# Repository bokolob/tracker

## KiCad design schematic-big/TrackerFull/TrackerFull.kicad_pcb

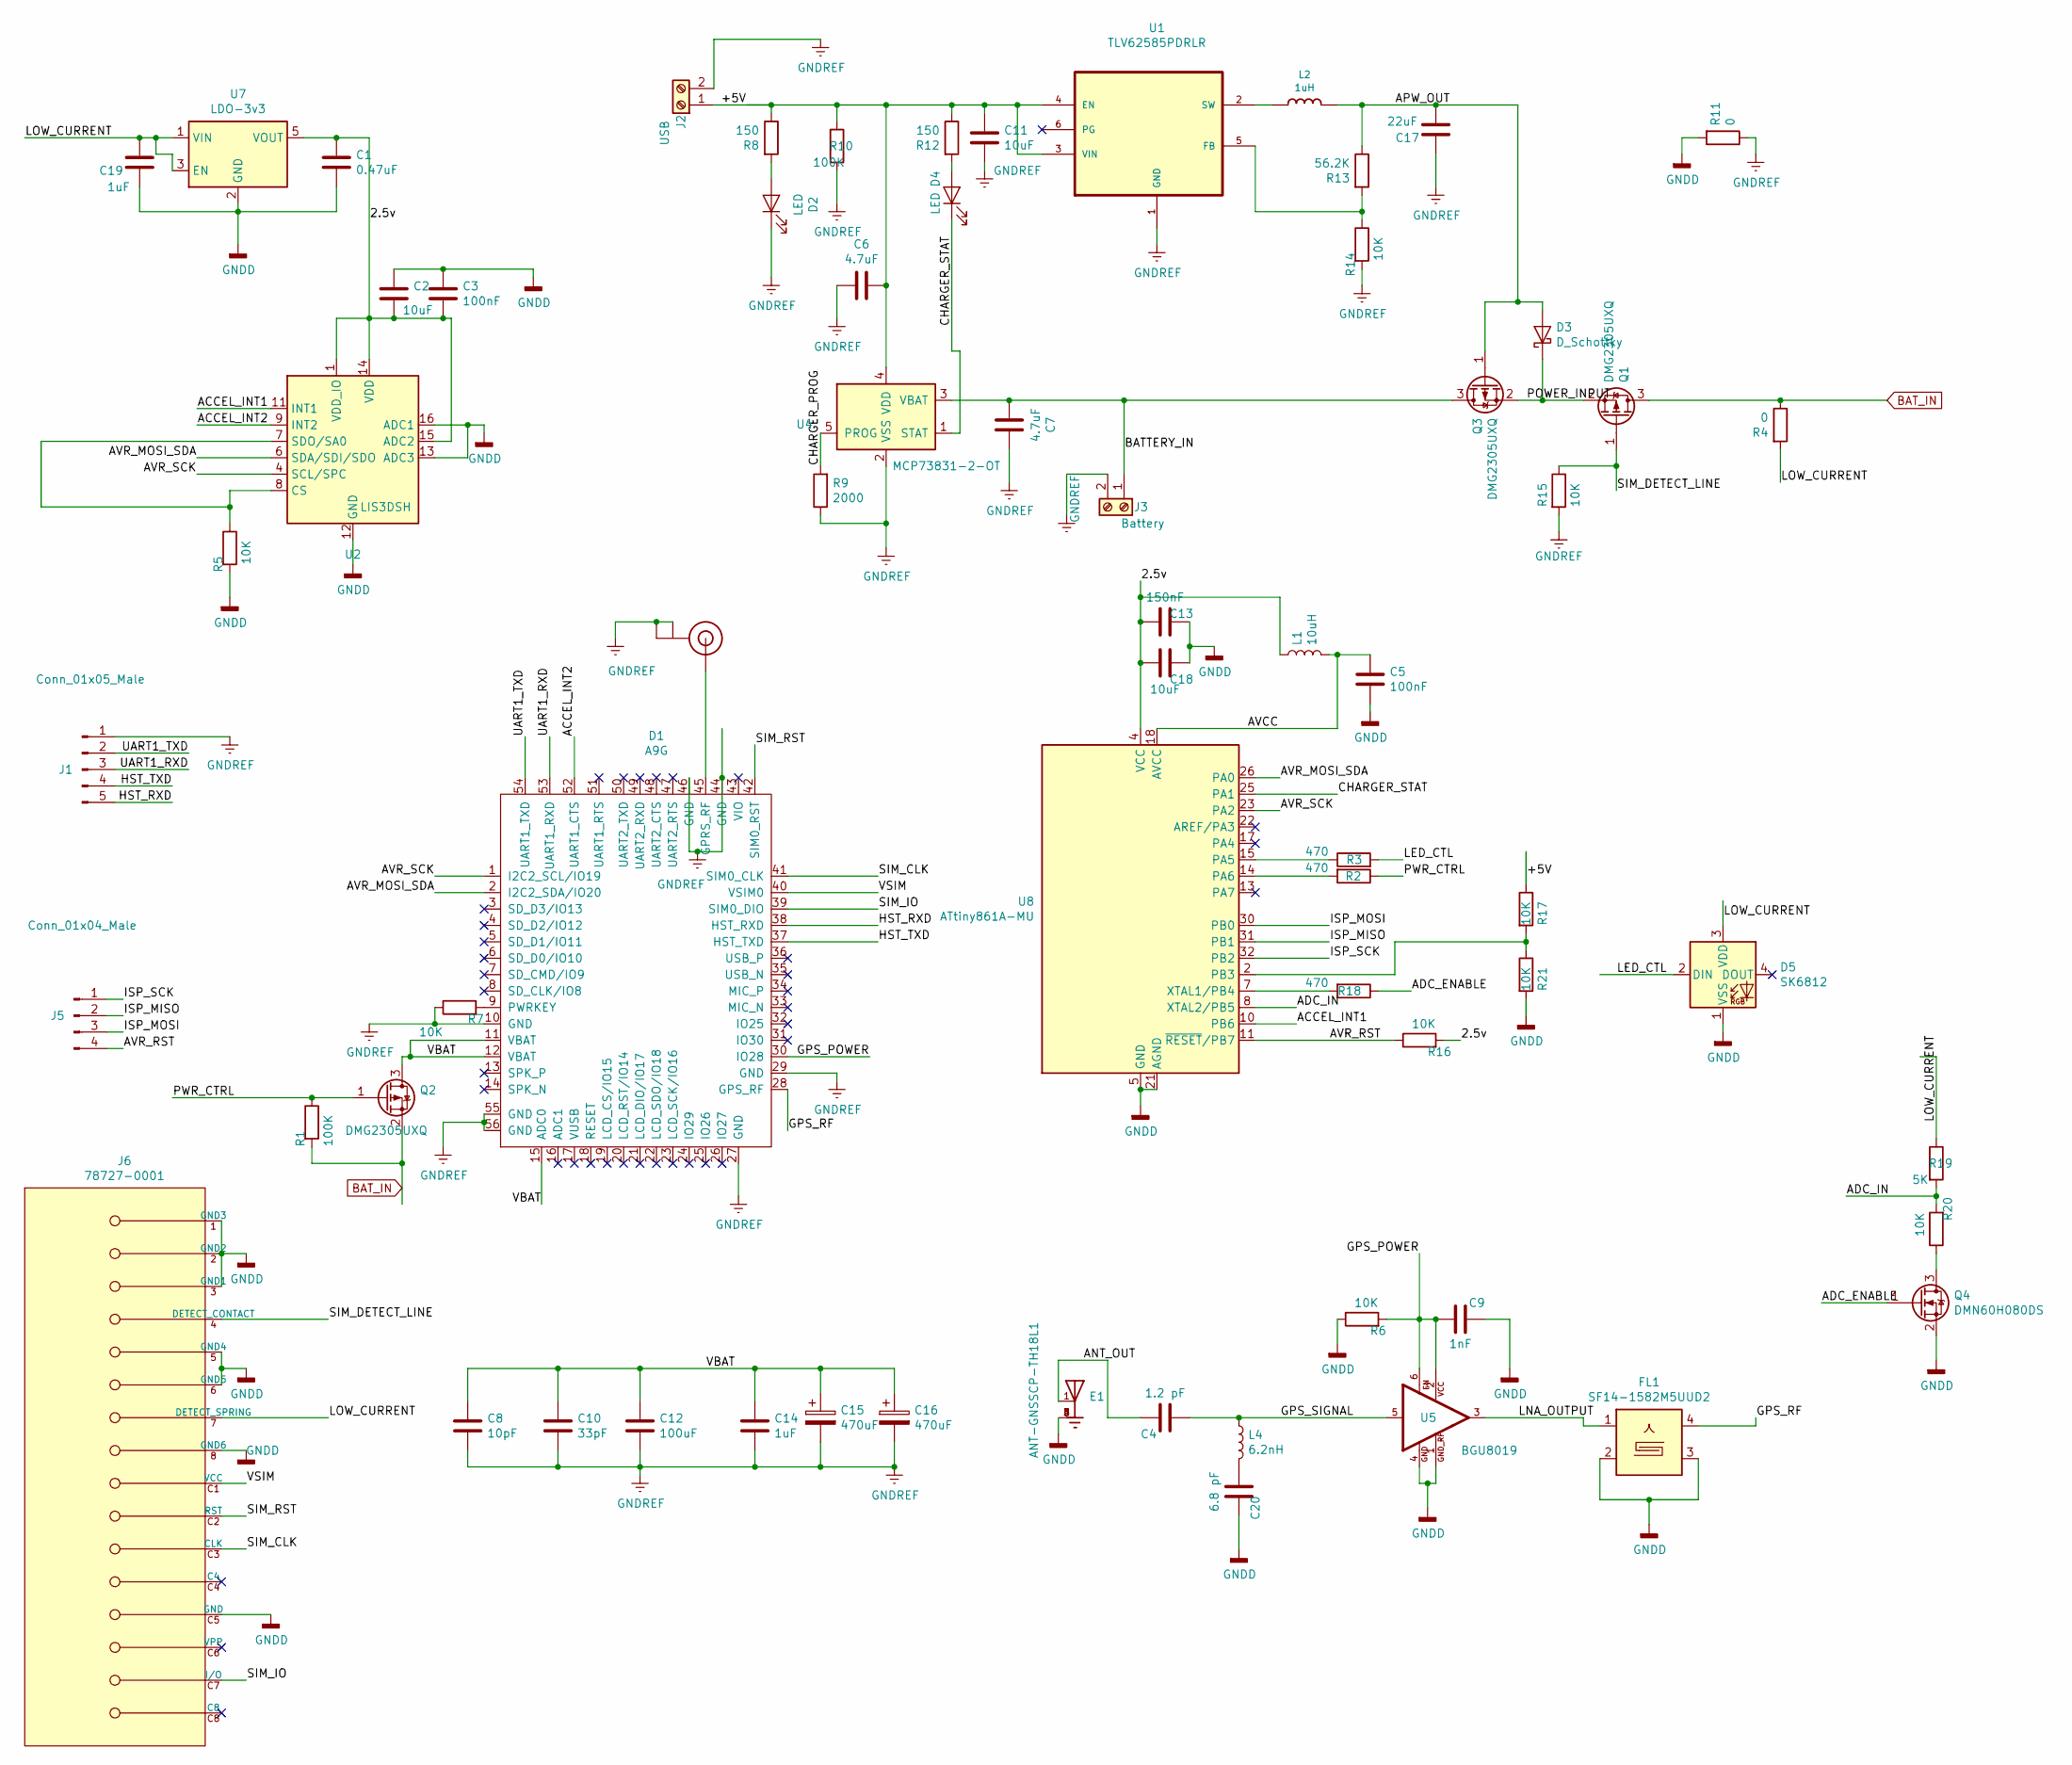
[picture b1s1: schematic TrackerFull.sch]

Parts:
C1: 0.47uF; C_0603_1608Metric
C2, C11, C18: 10uF; C_0603_1608Metric
C3, C5: 100nF; C_0402_1005Metric
C4: 1.2 pF; C_0402_1005Metric
C6, C7: 4.7uF; C_0603_1608Metric
C8: 10pF; C_0402_1005Metric
C9: 1nF; C_0402_1005Metric
C10: 33pF; C_0402_1005Metric
C12: 100uF; CP_EIA-6032-28_Kemet-C
C13: 150nF; C_0402_1005Metric
C14, C19: 1uF; C_0603_1608Metric
C15, C16: 470uF; CP_Elec_8x10.5
C17: 22uF; C_0805_2012Metric
C20: 6.8 pF; C_0402_1005Metric
D1: A9G; A9
D2, D4: LED; LED_0603_1608Metric_Pad1.05x0.95mm_HandSolder
D3: D_Schottky; D_SMA
D5: SK6812; LED_SK6812_PLCC4_5.0x5.0mm_P3.2mm
E1: ANT-GNSSCP-TH18L1; XDCR_ANT-GNSSCP-TH18L1
FL1: SF14-1582M5UUD2; Filter_1411-5_1.4x1.1mm
J1: Conn_01x05_Male; PinHeader_1x05_P2.54mm_Vertical
J2: USB; SolderWirePad_1x02_P3.81mm_Drill0.8mm
J3: Battery; SolderWirePad_1x02_P3.81mm_Drill0.8mm
J5: Conn_01x04_Male; PinHeader_1x04_P2.54mm_Vertical
J6: 78727-0001; Molex-78727-0001-0-0-MFG
L1: 10uH; L_0603_1608Metric
L2: 1uH; L_Vishay_IHLP-2020
L4: 6.2nH; L_0402_1005Metric
Q1, Q2, Q3: DMG2305UXQ; SOT-23
Q4: DMN60H080DS; SOT-23
R1, R10: 100K; R_0603_1608Metric
R2, R3, R18: 470; R_0402_1005Metric
R4, R11: 0; R_0402_1005Metric
R5, R6, R7, R14, R15, R16, R17, R20: 10K; R_0603_1608Metric
R8, R12: 150; R_0402_1005Metric
R9: 2000; R_0402_1005Metric
R13: 56.2K; R_0603_1608Metric
R19: 5K; R_0402_1005Metric
R21: 10K; R_0402_1005Metric
U1: TLV62585PDRLR; SOT50P160X60-6N
U2: LIS3DSH; LGA-16_3x3mm_P0.5mm_LayoutBorder3x5y
U4: MCP73831-2-OT; SOT-23-5
U5: BGU8019; SOT1232
U6: U.FL
U7: LDO-3v3; SOT-23-5
U8: ATtiny861A-MU; QFN-32-1EP_5x5mm_P0.5mm_EP3.1x3.1mm

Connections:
/2.5v: C1.1, C2.2, C3.2, C13.2, C18.2, L1.1, R16.2, U2.1 (VDD_IO), U2.14 (VDD), U2.15 (ADC2), U7.5 (VOUT), U8.4 (VCC)
/+5V: C6.2, C11.1, J2.1, R8.1, R10.1, R12.1, R17.1, U1.3 (VIN), U1.4 (EN), U4.4 (VDD)
/ACCEL_INT1: U2.11 (INT1), U8.10 (PB6)
/ACCEL_INT2: D1.52 (UART1_CTS), U2.9 (INT2)
/ADC_ENABLE: Q4.1 (G), R18.1
/ADC_IN: R19.2, R20.2, U8.8 (XTAL2/PB5)
/ANT_OUT: C4.2, E1.1
/APW_OUT: C17.1, D3.2 (A), L2.2, Q3.1 (G), R13.1
/AVCC: C5.1, L1.2, U8.18 (AVCC)
/AVR_MOSI_SDA: D1.2 (I2C2_SDA/IO20), U2.6 (SDA/SDI/SDO), U8.26 (PA0)
/AVR_RST: J5.4, R16.1, U8.11 (~RESET~/PB7)
/AVR_SCK: D1.1 (I2C2_SCL/IO19), U2.4 (SCL/SPC), U8.23 (PA2)
/BATTERY_IN: C7.1, J3.1, Q3.3 (D), U4.3 (VBAT)
/CHARGER_PROG: R9.2, U4.5 (PROG)
/CHARGER_STAT: D4.1 (K), U4.1 (STAT), U8.25 (PA1)
/GPS_POWER: C9.1, D1.30 (IO28), R6.2, U5.2, U5.6
/GPS_RF: D1.28 (GPS_RF), FL1.4
/GPS_SIGNAL: C4.1, L4.1, U5.5
/HST_RXD: D1.38 (HST_RXD), J1.5
/HST_TXD: D1.37 (HST_TXD), J1.4
/ISP_MISO: J5.2, U8.31 (PB1)
/ISP_MOSI: J5.3, U8.30 (PB0)
/ISP_SCK: J5.1, U8.32 (PB2)
/LED_CTL: D5.2 (DIN), R3.2
/LNA_OUTPUT: FL1.1, U5.3
/LOW_CURRENT: C19.1, D5.3 (VDD), J6.7 (DETECT_SPRING), R4.2, R19.1, U7.1 (VIN), U7.3 (EN)
/POWER_INPUT: D3.1 (K), Q1.2 (S), Q3.2 (S)
/PWR_CTRL: Q2.1 (G), R1.1, R2.1
/SIM_CLK: D1.41 (SIM0_CLK), J6.C3 (CLK)
/SIM_DETECT_LINE: J6.4 (DETECT_CONTACT), Q1.1 (G), R15.1
/SIM_IO: D1.39 (SIM0_DIO), J6.C7 (I/O)
/SIM_RST: D1.42 (SIM0_RST), J6.C2 (RST)
/UART1_RXD: D1.53 (UART1_RXD), J1.3
/UART1_TXD: D1.54 (UART1_TXD), J1.2
/VBAT: C8.1, C10.1, C12.1, C14.1, C15.1, C16.1, D1.11 (VBAT), D1.12 (VBAT), D1.15 (ADC0), Q2.3 (D)
/VSIM: D1.40 (VSIM0), J6.C1 (VCC)
BAT_IN: Q1.3 (D), Q2.2 (S), R1.2, R4.1
GNDD: C1.2, C2.1, C3.1, C5.2, C9.2, C13.1, C18.1, C19.2, C20.2, D5.1 (VSS), E1.2, E1.3, E1.4, E1.5, FL1.2, FL1.3, FL1.5, J6.1 (GND3), J6.2 (GND2), J6.3 (GND1), J6.5 (GND4), J6.6 (GND5), J6.8 (GND6), J6.C5 (GND), Q4.2 (S), R5.2, R6.1, R11.2, R21.2, U2.5 (GND), U2.10 (GND), U2.12 (GND), U2.13 (ADC3), U2.16 (ADC1), U5.1, U5.4, U7.2 (GND), U8.5 (GND), U8.21 (AGND), U8.33 (GND)
GNDREF: C6.1, C7.2, C8.2, C10.2, C11.2, C12.2, C14.2, C15.2, C16.2, C17.2, D1.10 (GND), D1.27 (GND), D1.29 (GND), D1.44 (GND), D1.46 (GND), D1.55 (GND), D1.56 (GND), D2.1 (K), J1.1, J2.2, J3.2, R7.1, R9.1, R10.2, R11.1, R14.2, R15.2, U1.1 (GND), U4.2 (VSS), U6.1 (GND@0), U6.2 (GND@1)
unnamed: C20.1, L4.2
unnamed: D1.9 (PWRKEY), R7.2
unnamed: D1.45 (GPRS_RF), U6.3 (SIGNAL)
unnamed: D2.2 (A), R8.2
unnamed: D4.2 (A), R12.2
unnamed: L2.1, U1.2 (SW)
unnamed: Q4.3 (D), R20.1
unnamed: R2.2, U8.14 (PA6)
unnamed: R3.1, U8.15 (PA5)
unnamed: R5.1, U2.7 (SDO/SA0), U2.8 (CS)
unnamed: R13.2, R14.1, U1.5 (FB)
unnamed: R17.2, R21.1, U8.2 (PB3)
unnamed: R18.2, U8.7 (XTAL1/PB4)

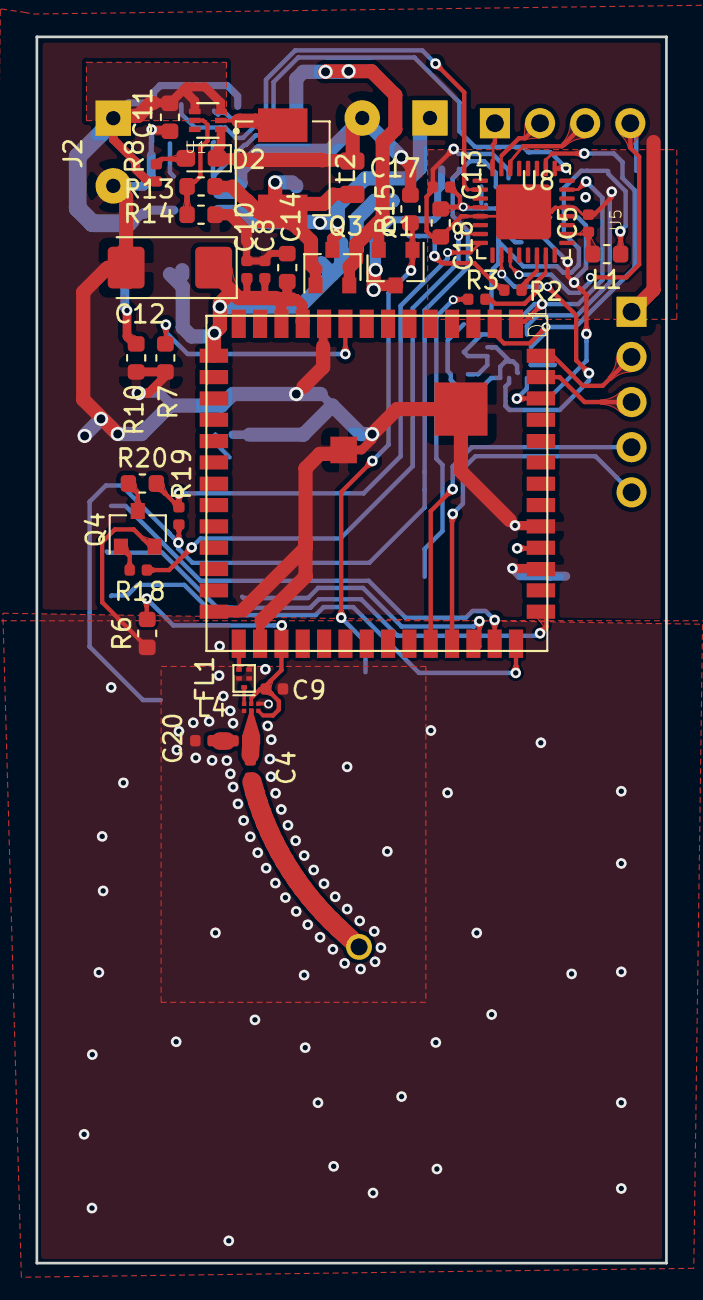
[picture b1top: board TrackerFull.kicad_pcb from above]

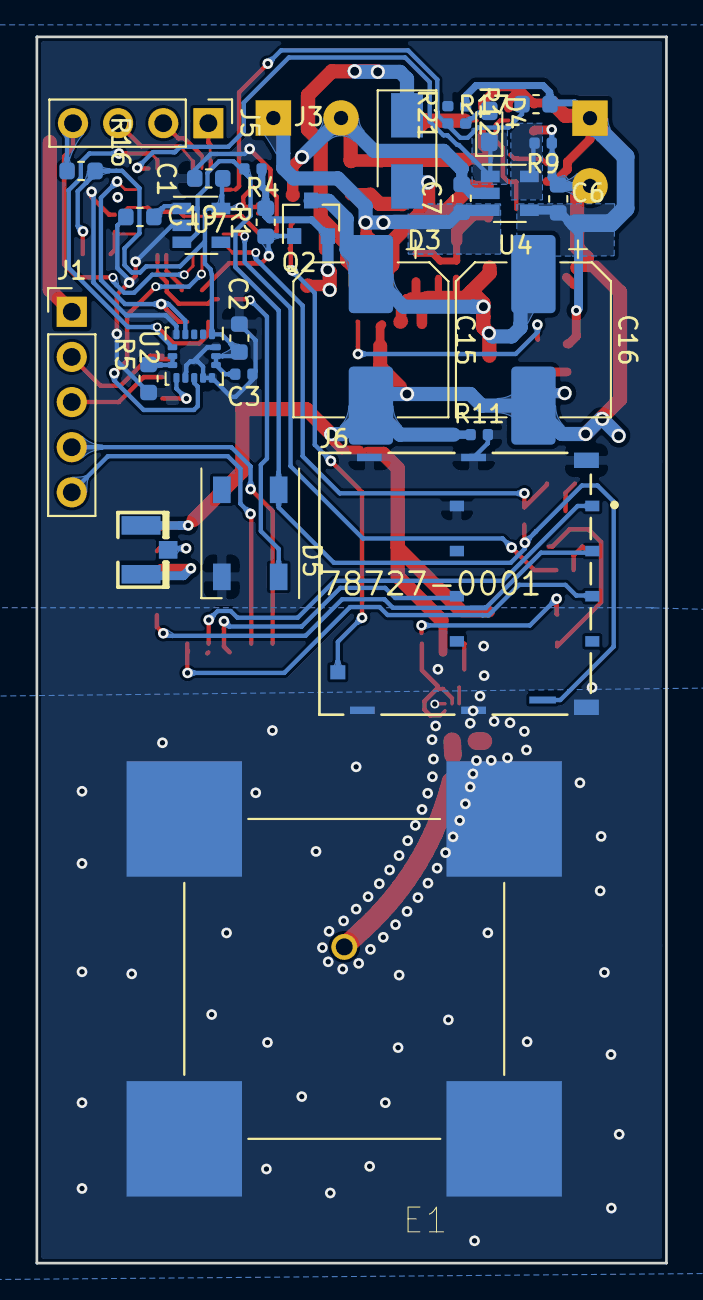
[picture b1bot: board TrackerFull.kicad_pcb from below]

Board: 2 copper layers, 35.4 x 69.0 mm, 67 parts (30 on the bottom side), 52 nets.

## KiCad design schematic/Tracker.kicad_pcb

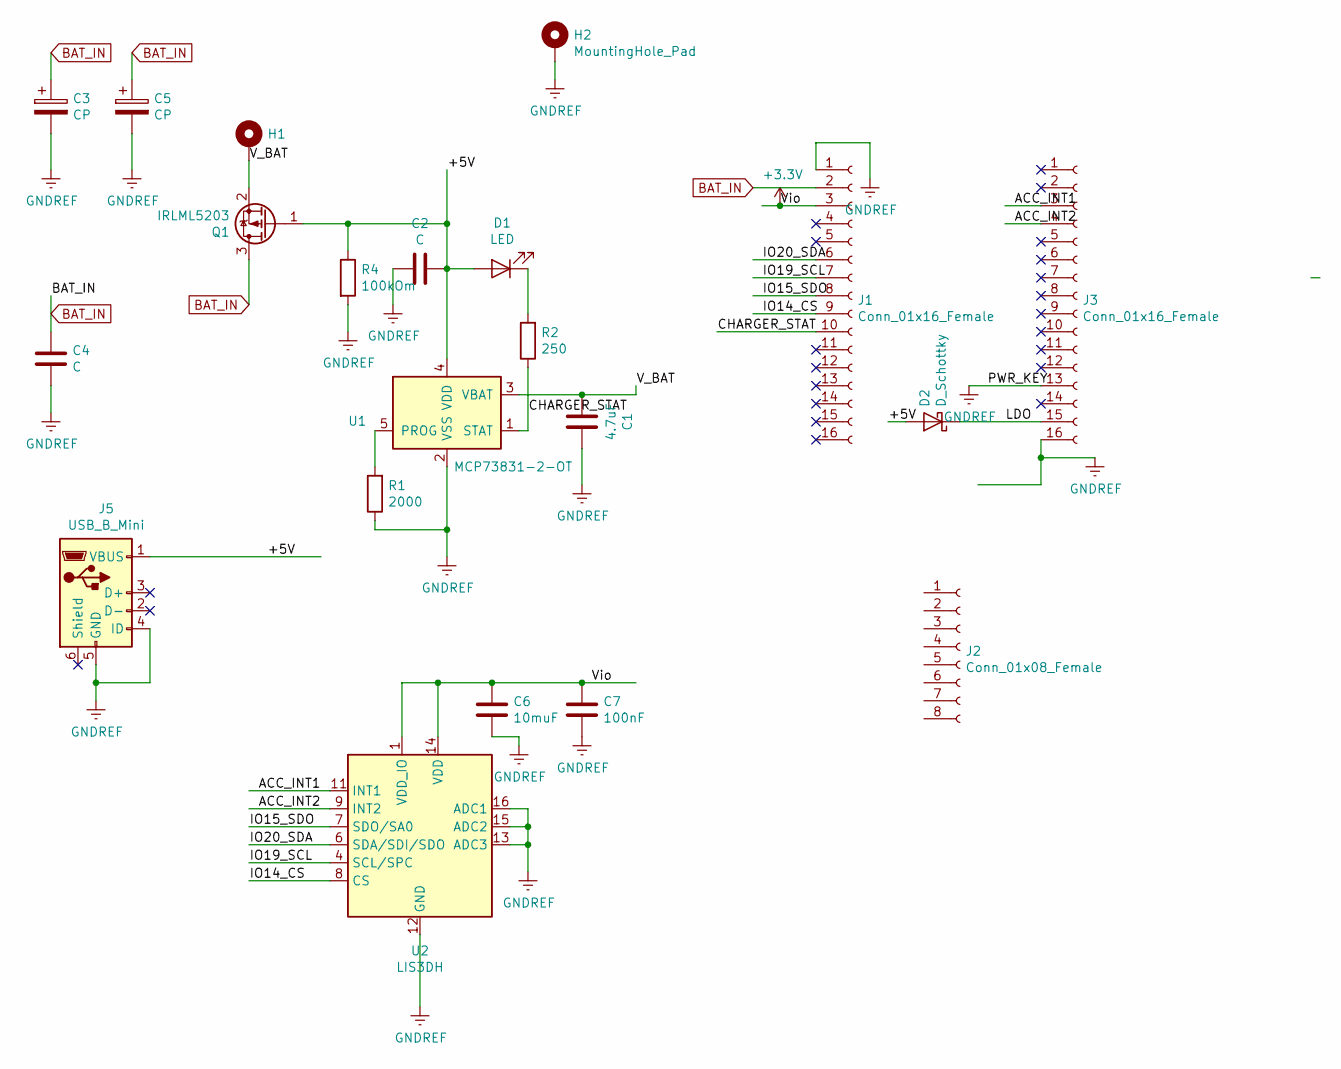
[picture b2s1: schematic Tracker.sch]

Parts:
C1: 4.7uF; CP_Radial_D4.0mm_P2.00mm
C2: C; CP_Radial_D4.0mm_P2.00mm
C3, C5: CP; CP_Radial_D8.0mm_P3.50mm
C4: C; CP_EIA-3216-18_Kemet-A
C6: 10muF; C_Disc_D3.4mm_W2.1mm_P2.50mm
C7: 100nF; C_Disc_D3.4mm_W2.1mm_P2.50mm
D1: LED; LED_D3.0mm
D2: D_Schottky; D_SMA
H1, H2: MountingHole_Pad; MountingHole_2.2mm_M2_DIN965_Pad
J1, J3: Conn_01x16_Female; PinSocket_1x16_P2.54mm_Vertical
J2: Conn_01x08_Female; PinHeader_1x08_P2.54mm_Vertical
J5: USB_B_Mini; USB_Micro-B_Molex-105017-0001
Q1: IRLML5203; SOT-23
R1: 2000; R_0603_1608Metric
R2: 250; R_0402_1005Metric
R4: 100kOm; R_0603_1608Metric
U1: MCP73831-2-OT; SOT-23-5
U2: LIS3DH; LGA-16_3x3mm_P0.5mm_LayoutBorder3x5y

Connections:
+3V3: C6.1, C7.1, J1.3, U2.1 (VDD_IO), U2.14 (VDD)
/+5V: C2.2, D1.2 (A), D2.2 (A), J5.1 (VBUS), Q1.1 (G), R4.1, U1.4 (VDD)
/ACC_INT1: J3.3, U2.11 (INT1)
/ACC_INT2: J3.4, U2.9 (INT2)
/CHARGER_STAT: J1.10, R2.1, U1.1 (STAT)
/IO14_CS: J1.9, U2.8 (CS)
/IO15_SDO: J1.8, U2.7 (SDO/SA0)
/IO19_SCL: J1.7, U2.4 (SCL/SPC)
/IO20_SDA: J1.6, U2.6 (SDA/SDI/SDO)
/LDO: D2.1 (K), J3.15
/V_BAT: C1.1, H1.1, Q1.2 (S), U1.3 (VBAT)
BAT_IN: C3.1, C4.1, C5.1, J1.2, Q1.3 (D)
GNDREF: C1.2, C2.1, C3.2, C4.2, C5.2, C6.2, C7.2, H2.1, J1.1, J3.13, J3.16, J5.4 (ID), J5.5 (GND), R1.1, R4.2, U1.2 (VSS), U2.5 (GND), U2.10 (GND), U2.12 (GND), U2.13 (ADC3), U2.15 (ADC2), U2.16 (ADC1)
unnamed: D1.1 (K), R2.2
unnamed: R1.2, U1.5 (PROG)

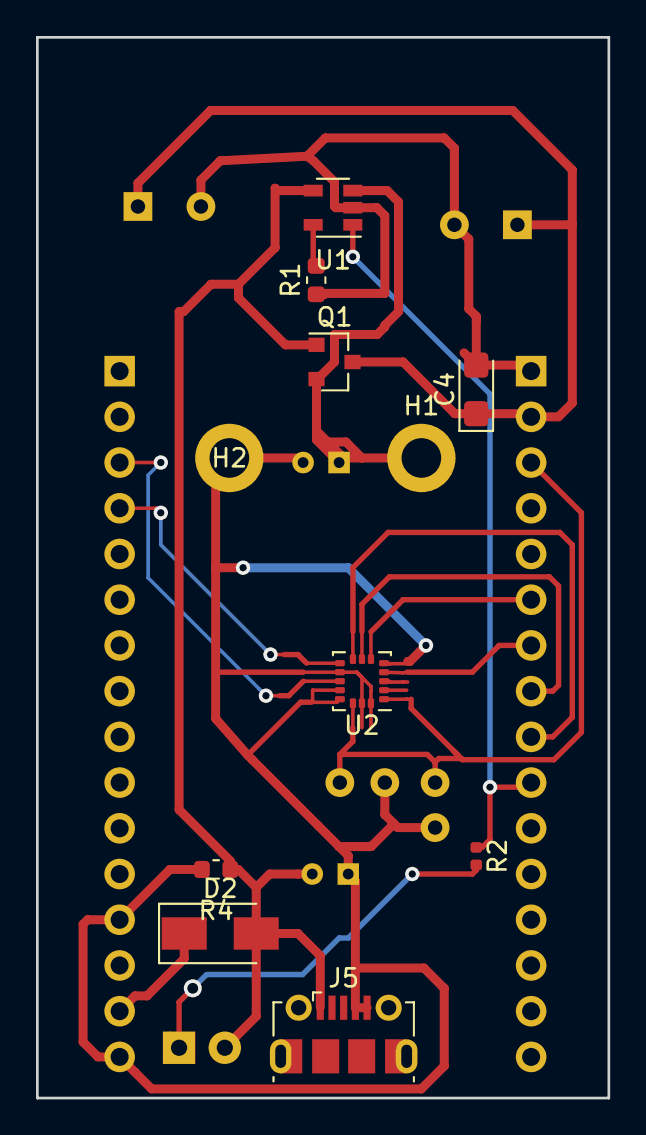
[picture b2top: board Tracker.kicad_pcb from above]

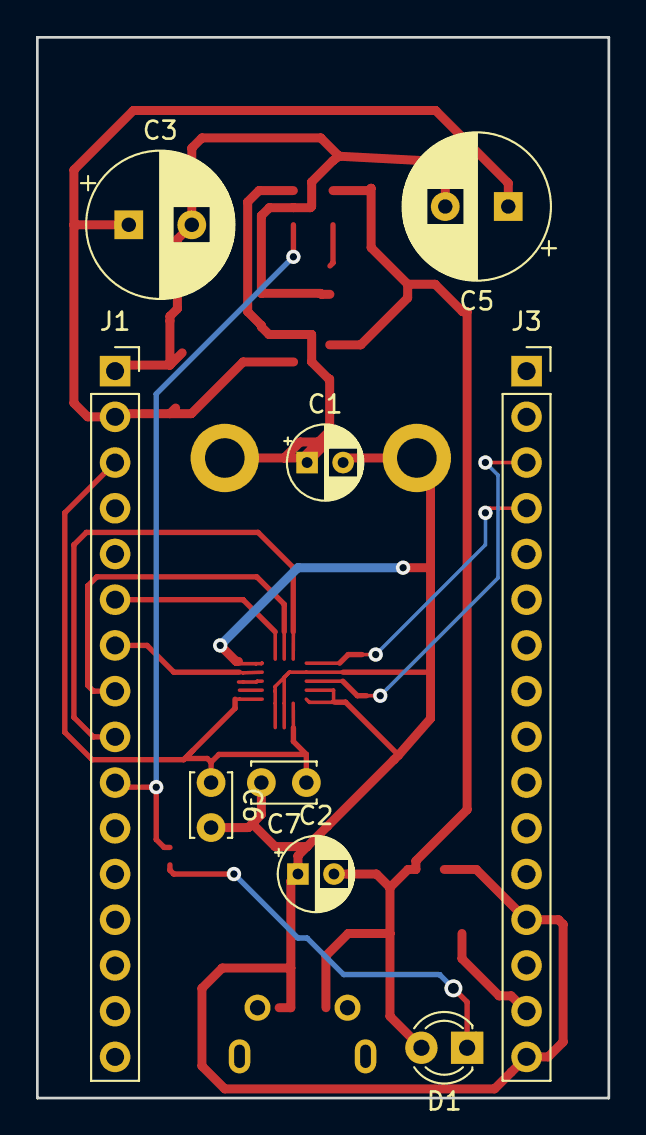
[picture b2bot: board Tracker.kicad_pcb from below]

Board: 2 copper layers, 31.8 x 58.9 mm, 20 parts (9 on the bottom side), 15 nets.

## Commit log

2020-07-17 Lis3dsh accel driver
2020-07-28 Schematics
2020-08-07 multiple improvements
2020-09-09 Sms commands and refactorings
2020-09-10 New schematic
2020-09-10 schematic.png
2020-09-10 schematic fixes
2020-09-14 bug fixes
2020-09-19 schematic update
2020-09-30 Software i2c
2020-10-08 Last avr firmvare
2020-10-08 Last schematic
2020-10-12 latest version. Doesnt work :)
2020-10-13 last changes
2020-10-17 new schematic picture
2020-10-22 schematic updated
2020-10-26 next milestone
2020-10-28 GPS antenna on pcb
2020-10-30 updated schematic
2020-11-06 Last schematic changes
2020-11-08 schematics update
2020-11-10 replaced attiny
2020-11-14 pcb layout
2020-11-20 attiny461 code update and new a9g footprint
2020-11-21 last schematic update
2020-12-05 pcb update
2020-12-09 last pcb version
2020-12-18 Incoming connections handler
2020-12-18 server updates
2020-12-23 Serverside update
2020-12-25 Fixes
2020-12-29 better ux
2020-12-30 trackerbot
2021-01-02 server
2021-01-04 Shared devices
2021-01-10 improvements
2021-01-25 websockets
2021-01-27 Trackers moved to separate vue components
2021-01-27 Added previously forgotten components to git
